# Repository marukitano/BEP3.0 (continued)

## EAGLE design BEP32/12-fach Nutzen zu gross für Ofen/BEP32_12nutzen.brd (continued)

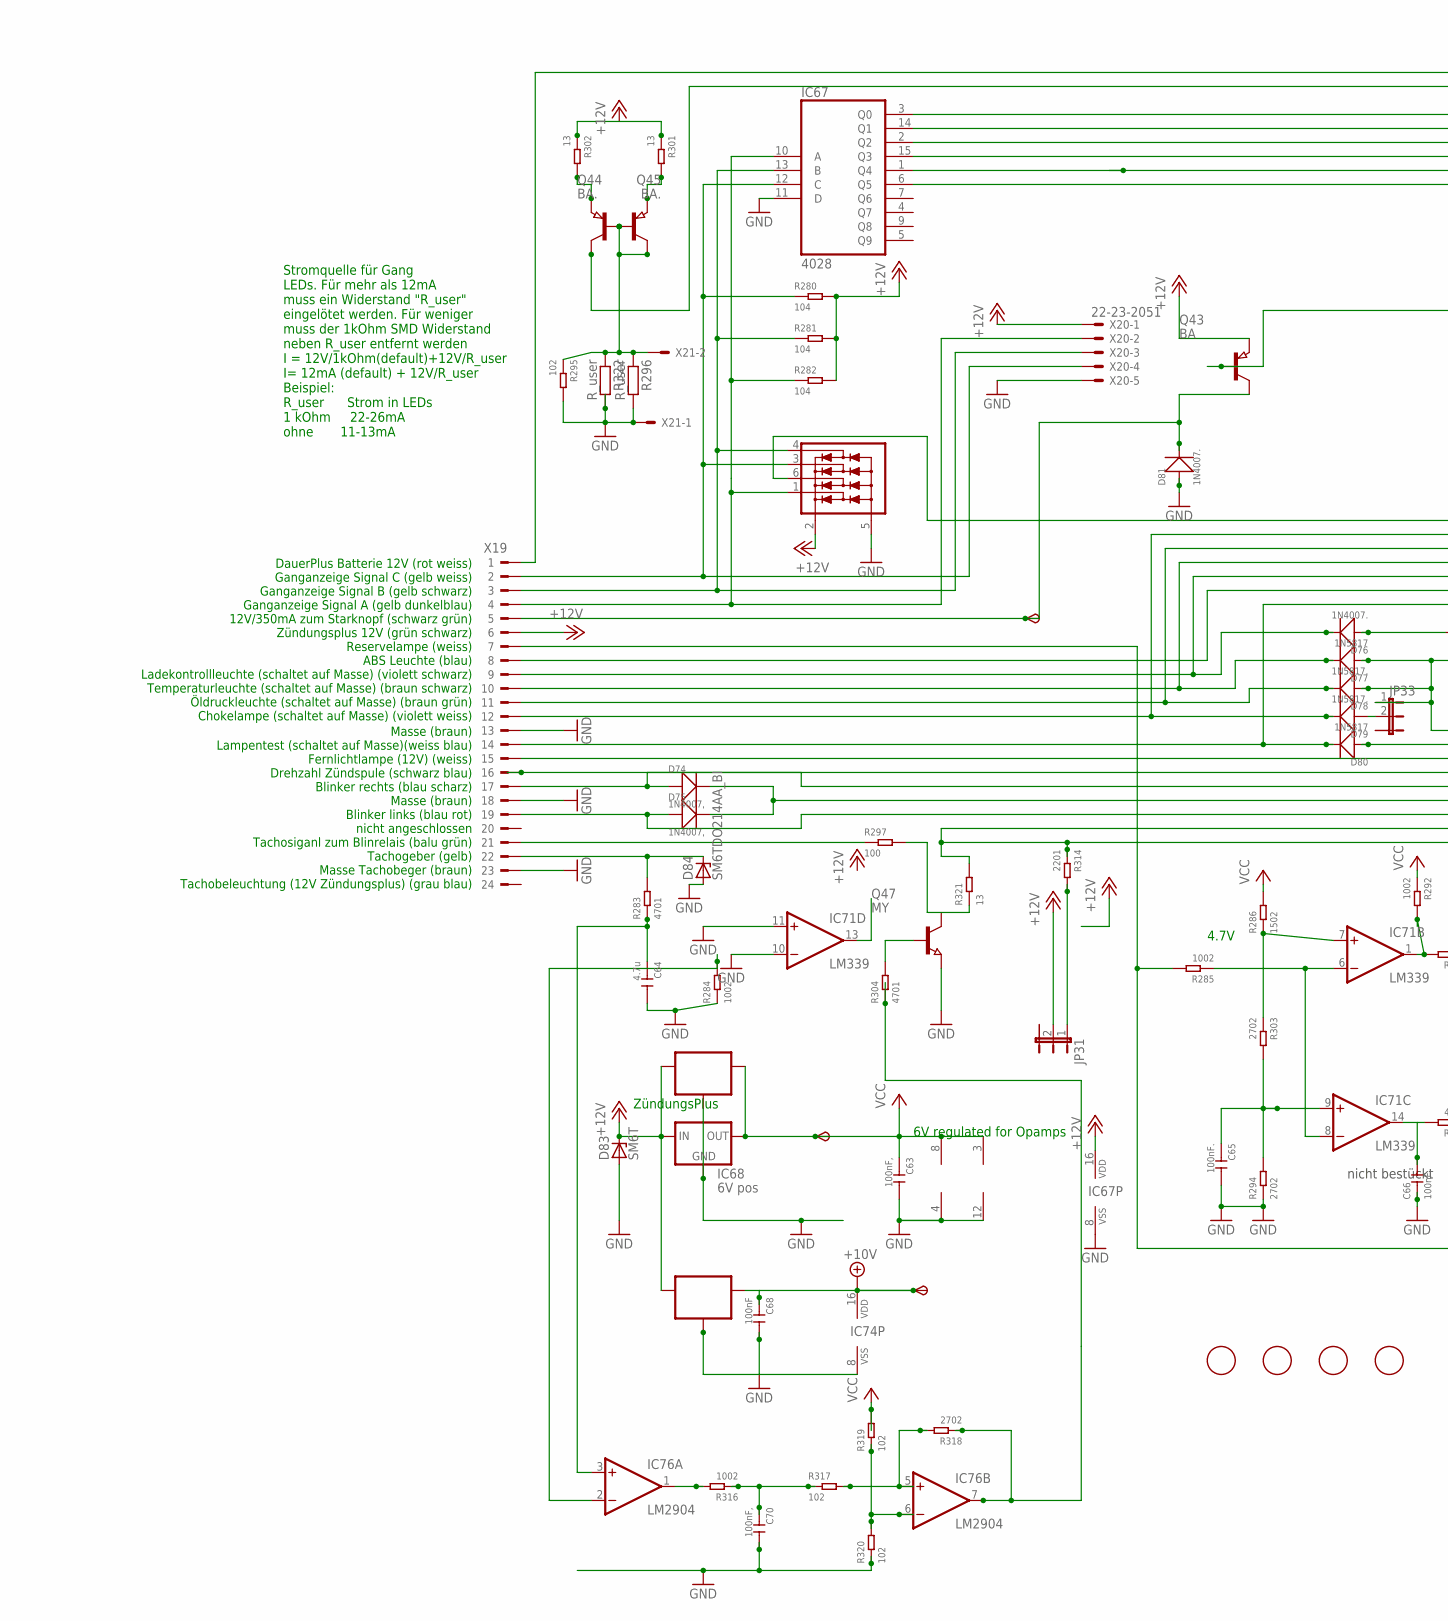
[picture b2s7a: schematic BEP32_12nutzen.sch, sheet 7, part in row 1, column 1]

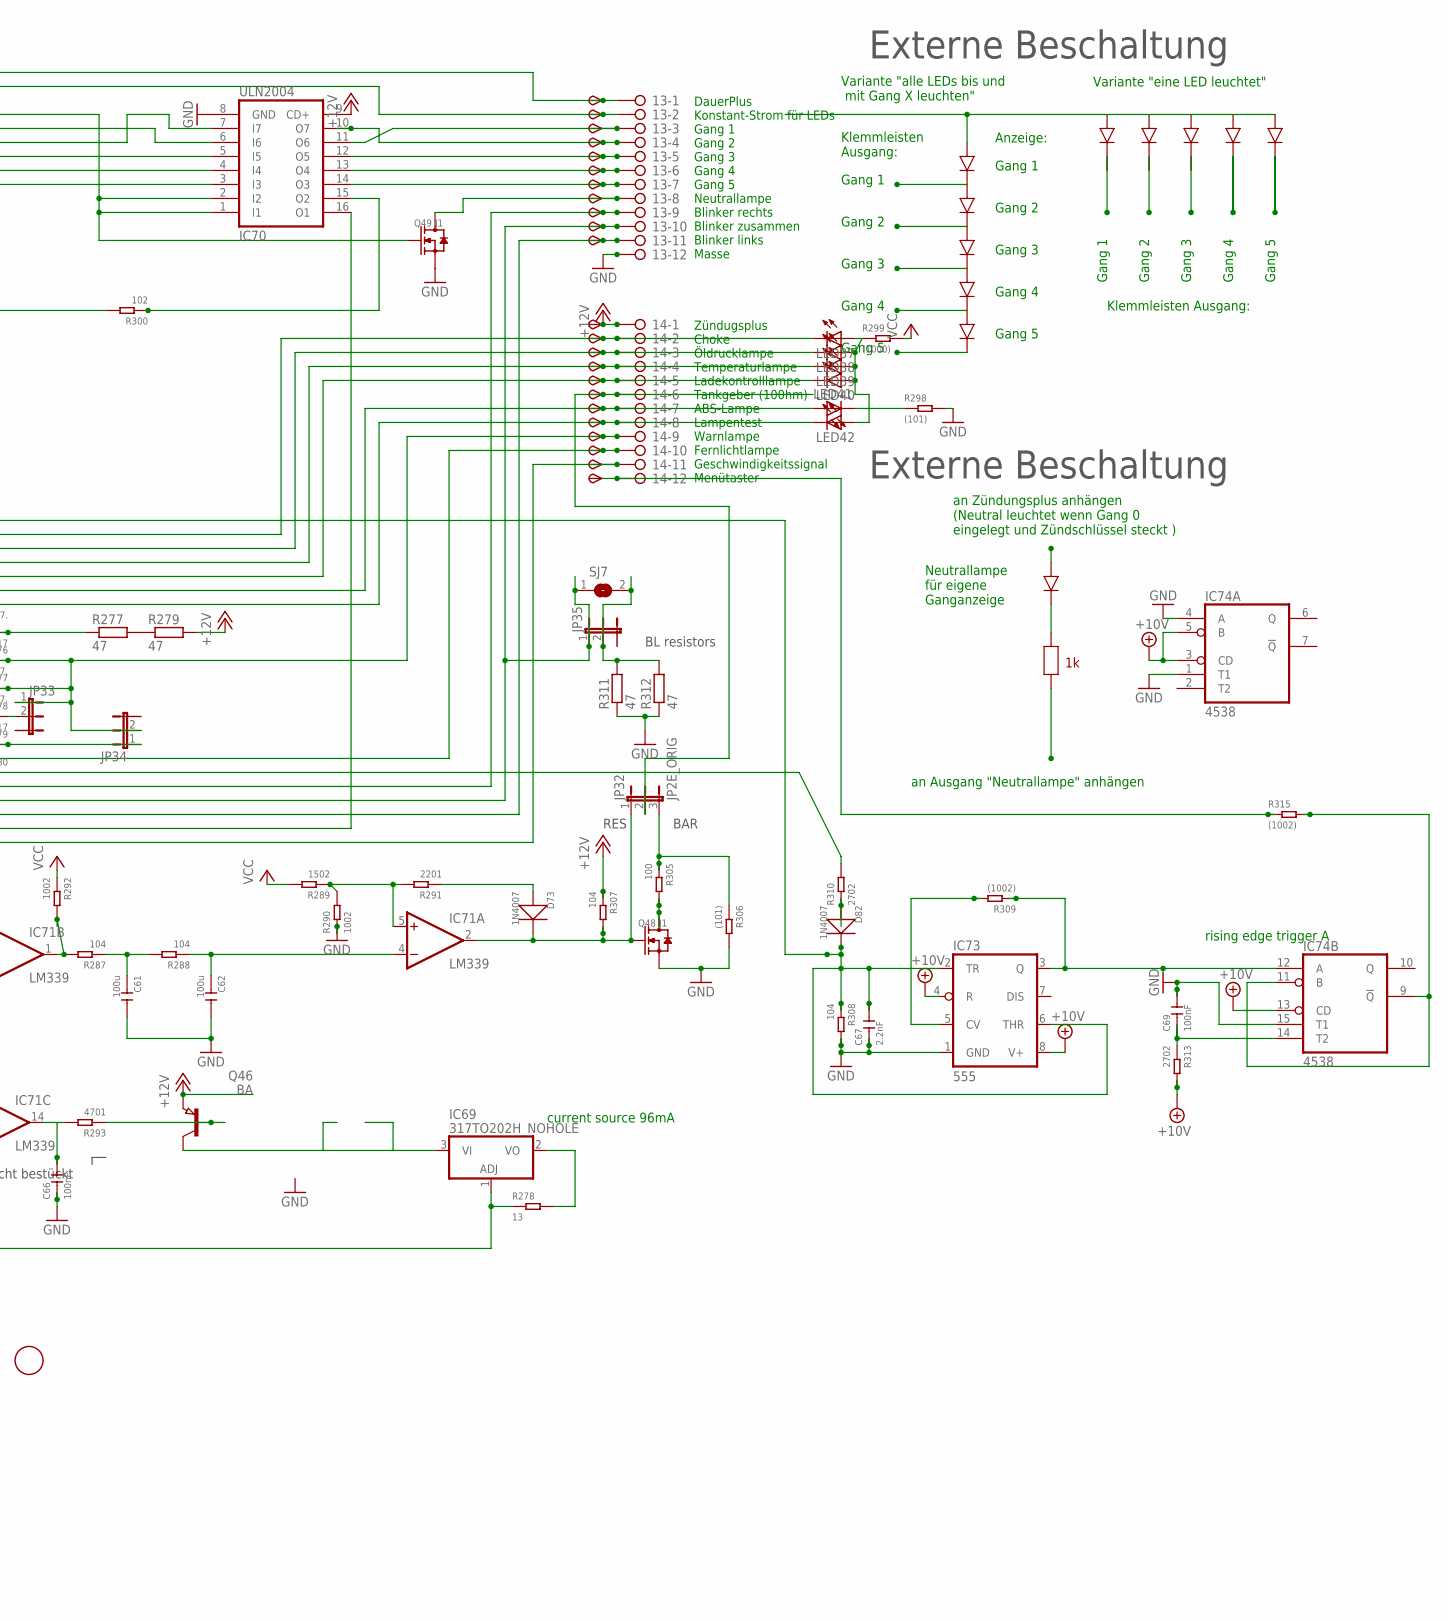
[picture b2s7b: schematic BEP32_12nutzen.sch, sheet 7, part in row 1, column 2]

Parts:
6V6, 10V6: TPSB2.0; B2.0
13, 14: 2081-1132; 12-PIN
C61, C62: 100u; C1206
C63, C70: 100nF,; C0805
C64: 4.7u; C0805
C65, C66: 100nF.; C0805
C67: 2.2nF; C0805
C68, C69: 100nF; C0805
D73, D82: 1N4007; DO-214AC
D74, D75: 1N4007,; DO-214AC
D76, D81: 1N4007.; DO-214AC
D77, D80: 1N5817; DO-214AC_SLIM
D78, D79: 1N5817.; DO-214AC_SLIM
D83: SM6T; DO214AA
D84: SM6TDO214AA_BI; DO214AA_BI
FID25, FID26, FID27, FID28: FIDUCIAL; FIDUCIAL_1MM
IC67: 4028; SO16
IC68: 6V pos; 78LXX
IC69: 317TO202H_NOHOLE; TO220H_NOHOLE
IC70: ULN2004; SO16
IC71: LM339; SO14
IC72: 78L06; SOT89_ROUND
IC73: 555; SO08
IC74: 4538; SO16
IC75: 78L10; SOT89_ROUND
IC76: LM2904; SO08
IC77: NUP4304SOT457_R; SOT457R_PHILIPS
JP31, JP33, JP34, JP35: JP2EJP2_SMALLPADS; JP2_SMALLPADS
JP32: JP2E_ORIG; JP2_ORIG_SMALLPADS
LED37, LED38, LED39, LED40, LED41, LED42: LEDLD260; LD260
Q43, Q46: BA; SOT89
Q44, Q45: BA.; SOT89
Q47: MY; SOT89
Q48, Q49: J1; SOT-23
R277, R279, R311, R312: 47; V235/17_1MM
R278, R301, R302, R321: 13; R1206
R280, R281, R282, R287, R288, R307, R308: 104; R0805
R283, R293, R304: 4701; R0805
R284, R285, R290, R292, R316: 1002; R0805
R286, R289: 1502; R0805
R291, R314: 2201; R0805
R294, R303, R310, R313, R318: 2702; R0805
R295, R300, R317, R319, R320: 102; R0805
R296, R322: R_user; R0805
R297, R305: 100; R0805
R298, R306: (101); R0805
R299: (1000); R0805
R309, R315: (1002); R0805
SJ7: SJ
START6: TPSB2.0; B2.0
TP139, TP140, TP141, TP142, TP143, TP144, TP145, TP146, TP147, TP148, TP149, TP150, TP151, TP152, TP153, TP154, TP155, TP156, TP158, TP159, TP160, TP161: TPSB2.0; B2.0
TP157: TPSB1,27; B1,27
X19: CON_BMWV2; 24-PIN_V2
X20: 22-23-2051
X21: 22-23-2021

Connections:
+10V: 10V6.TP, C68.1, IC73.4 (R), IC73.8 (V+), IC74.3 (CD), IC74.5 (B), IC74.13 (CD), IC74.16 (VDD), IC75.1 (OUT), R313.2; also elsewhere on the board
+12V: 14.1, D83.C, IC67.16 (VDD), IC68.IN, IC70.9 (CD+), IC72.3 (IN), IC75.3 (IN), IC77.2 (V+), JP31.2, Q43.3 (E), Q46.3 (E), R279.2, R280.2, R281.2, R282.2, R301.1, R302.1, R307.1, TP160.TP, X19.6, X20.1; also elsewhere on the board
+12V7: IC76.7 (OUT), R304.1, R318.1
GND: 13.12, C61.2, C62.2, C63.2, C64.2, C65.2, C66.1, C67.1, C68.2, C69.2, C70.2, D81.1 (+), D83.A, D84.A, IC67.8 (VSS), IC67.11 (D), IC68.GND, IC70.8 (GND), IC71.10 (-IN), IC71.11 (+IN), IC71.12 (GND), IC72.2 (GND), IC72.2@1 (GND), IC73.1 (GND), IC74.1 (T1), IC74.4 (A), IC74.8 (VSS), IC74.15 (T1), IC75.2 (GND), IC75.2@1 (GND), IC76.4 (V-), IC77.5 (V-), Q47.3 (E), Q48.2 (S), Q49.2 (S), R284.1, R290.1, R294.1, R295.2, R296.2, R298.2, R306.2, R308.2, R311.1, R312.1, R320.1, R322.2, X19.13, X19.18, X19.23, X20.5, X21.1; also elsewhere on the board
unnamed: R277.2, R279.1
unnamed: 14.9, D77.1 (+), D78.1 (+), JP33.1, JP34.2, TP157.TP
unnamed: IC67.10 (A), IC77.1 (D1), R282.1, X19.4, X20.2
unnamed: IC67.13 (B), IC77.4 (D4), R281.1, X19.3, X20.3
unnamed: D81.2 (-), Q43.2 (C), START6.TP, X19.5
unnamed: IC67.12 (C), IC77.3 (D3), R280.1, X19.2, X20.4
unnamed: 14.7, LED41.A, TP155.TP, X19.8
unnamed: 14.2, D79.2 (-), LED37.K (C), TP150.TP, X19.12
unnamed: 14.3, D78.2 (-), LED38.K (C), TP151.TP, X19.11
unnamed: 14.4, D77.2 (-), LED39.K (C), TP152.TP, X19.10
unnamed: 14.8, D80.2 (-), LED42.K (C), TP156.TP, X19.14
unnamed: 13.9, D74.1 (+), TP147.TP, X19.17
unnamed: 13.11, D75.1 (+), TP149.TP, X19.19
unnamed: D84.C, R283.2, X19.22
unnamed: C64.1, IC76.3 (+IN), R283.1
unnamed: 14.11, IC70.16 (O1), R314.1, R321.2, TP159.TP
unnamed: IC71.1 (OUT), R287.2, R292.2
unnamed: C61.1, R287.1, R288.2
unnamed: C62.1, IC71.4 (-IN), R288.1
unnamed: IC71.5 (+IN), R289.1, R290.2, R291.2
unnamed: D73.1 (+), R291.1
unnamed: C65.1, IC71.9 (+IN), R294.2, R303.2
unnamed: C66.2, IC71.14 (OUT), R293.2
unnamed: Q46.1 (B), R293.1
unnamed: IC67.2 (Q2), IC70.7 (I7)
unnamed: 13.5, IC70.12 (O5), TP143.TP
unnamed: IC67.1 (Q4), IC70.4 (I4)
unnamed: 13.8, Q49.3 (D), TP146.TP
unnamed: 14.10, TP158.TP, X19.15
unnamed: 14.5, D76.2 (-), LED40.K (C), TP153.TP, X19.9
unnamed: D76.1 (+), R277.1
unnamed: IC67.6 (Q5), IC70.3 (I3)
unnamed: 13.4, IC70.10 (O7), TP142.TP
unnamed: IC69.1 (ADJ), R278.1, R285.2, X19.7
unnamed: IC71.6 (-IN), IC71.8 (-IN), R285.1
unnamed: 13.2, Q45.2 (C), TP140.TP
unnamed: 13.1, TP139.TP, X19.1
unnamed: R310.2, X19.16
unnamed: IC67.15 (Q3), IC70.5 (I5)
unnamed: 13.6, IC70.13 (O4), TP144.TP
unnamed: 13.7, IC70.14 (O3), TP145.TP
unnamed: 14.6, JP32.2, TP154.TP
unnamed: LED41.K (C), R298.1
unnamed: LED37.A, LED38.A, LED39.A, LED40.A, LED42.A, R299.1
unnamed: Q43.1 (B), R300.2
unnamed: IC67.3 (Q0), IC70.1 (I1), IC70.2 (I2), Q49.1 (G)
unnamed: IC67.14 (Q1), IC70.6 (I6)
unnamed: 13.3, IC70.11 (O6), TP141.TP
unnamed: Q44.1 (B), Q44.2 (C), Q45.1 (B), R295.1, R296.1, R322.1, X21.2
unnamed: Q45.3 (E), R302.2
unnamed: Q44.3 (E), R301.2
unnamed: IC71.7 (+IN), R286.1, R303.1
unnamed: IC76.2 (-IN), R284.2
unnamed: Q47.1 (B), R304.2
unnamed: Q48.3 (D), R305.2
unnamed: IC69.2 (VO), R278.2
unnamed: IC69.3 (VI), Q46.2 (C)
unnamed: C67.2, D82.2 (-), IC73.2 (TR), IC73.6 (THR), IC77.6 (D2), R308.1
unnamed: IC73.5 (CV), R309.2
unnamed: IC73.3 (Q), IC74.12 (A), R309.1
unnamed: D82.1 (+), R310.1
unnamed: 13.10, D74.2 (-), D75.2 (-), JP35.1, SJ7.1, TP148.TP
unnamed: JP35.2, R311.2, R312.2, SJ7.2
unnamed: IC74.9 (!Q), IC74.11 (B), R315.2
unnamed: C69.1, IC74.14 (T2), R313.1
unnamed: JP31.1, R314.2
unnamed: IC70.15 (O2), R300.1
unnamed: 14.12, R315.1, TP161.TP
unnamed: D79.1 (+), JP33.2
unnamed: D73.2 (-), IC71.2 (OUT), JP32.1, Q48.1 (G), R307.2
unnamed: IC76.1 (OUT), R316.2
unnamed: C70.1, R316.1, R317.1
unnamed: IC76.5 (+IN), R317.2, R318.2
unnamed: IC76.6 (-IN), R319.1, R320.2
unnamed: D80.1 (+), JP34.1
unnamed: JP32.3, R305.1, R306.1
unnamed: R297.1, X19.21
unnamed: Q47.2 (C), R297.2, R321.1
VCC: 6V6.TP, C63.1, IC68.OUT, IC71.3 (V+), IC72.1 (OUT), IC76.8 (V+), R286.2, R289.2, R292.1, R299.2, R319.2; also elsewhere on the board

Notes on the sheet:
6V regulated for Opamps
current source 96mA
ZündungsPlus
Zündugsplus Choke Öldrucklampe Temperaturlampe Ladekontrolllampe Tankgeber (100hm) ABS-Lampe Lampentest Warnlampe Fernlichtlampe Geschwindigkeitssignal Menütaster
DauerPlus Konstant-Strom für LEDs Gang 1 Gang 2 Gang 3 Gang 4 Gang 5 Neutrallampe Blinker rechts Blinker zusammen Blinker links Masse
DauerPlus Batterie 12V (rot weiss) Ganganzeige Signal C (gelb weiss) Ganganzeige Signal B (gelb schwarz) Ganganzeige Signal A (gelb dunkelblau) 12V/350mA zum Starknopf (schwarz grün) Zündungsplus 12V (grün schwarz) Reservelampe (weiss) ABS Leuchte (blau) Ladekontrollleuchte (schaltet auf Masse) (vi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
Masse (braun) Lampentest (schaltet auf Masse)(weiss blau) Fernlichtlampe (12V) (weiss) Drehzahl Zündspule (schwarz blau) Blinker rechts (blau scharz) Masse (braun) Blinker links (blau rot) nicht angeschlossen Tachosiganl zum Blinrelais (balu grün) Tachogeber (gelb) Masse Tachobeger (braun) Tachobel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
4.7V
Stromquelle für Gang LEDs. Für mehr als 12mA muss ein Widerstand "R_user" eingelötet werden. Für weniger muss der 1kOhm SMD Widerstand neben R_user entfernt werden I = 12V/1kOhm(default)+12V/R_user I= 12mA (default) + 12V/R_user Beispiel: R_user Strom in LEDs 1 kOhm 22-26mA ohne 11-13mA
Gang 1
Gang 2
Gang 3
Gang 4
Gang 5
Variante "eine LED leuchtet"
Variante "alle LEDs bis und mit Gang X leuchten"
Klemmleisten Ausgang:
Klemmleisten Ausgang:
an Zündungsplus anhängen (Neutral leuchtet wenn Gang 0 eingelegt und Zündschlüssel steckt )
an Ausgang "Neutrallampe" anhängen
Neutrallampe für eigene Ganganzeige
Externe Beschaltung
Anzeige:
nicht bestückt
rising edge trigger A
BAR
RES
BL resistors

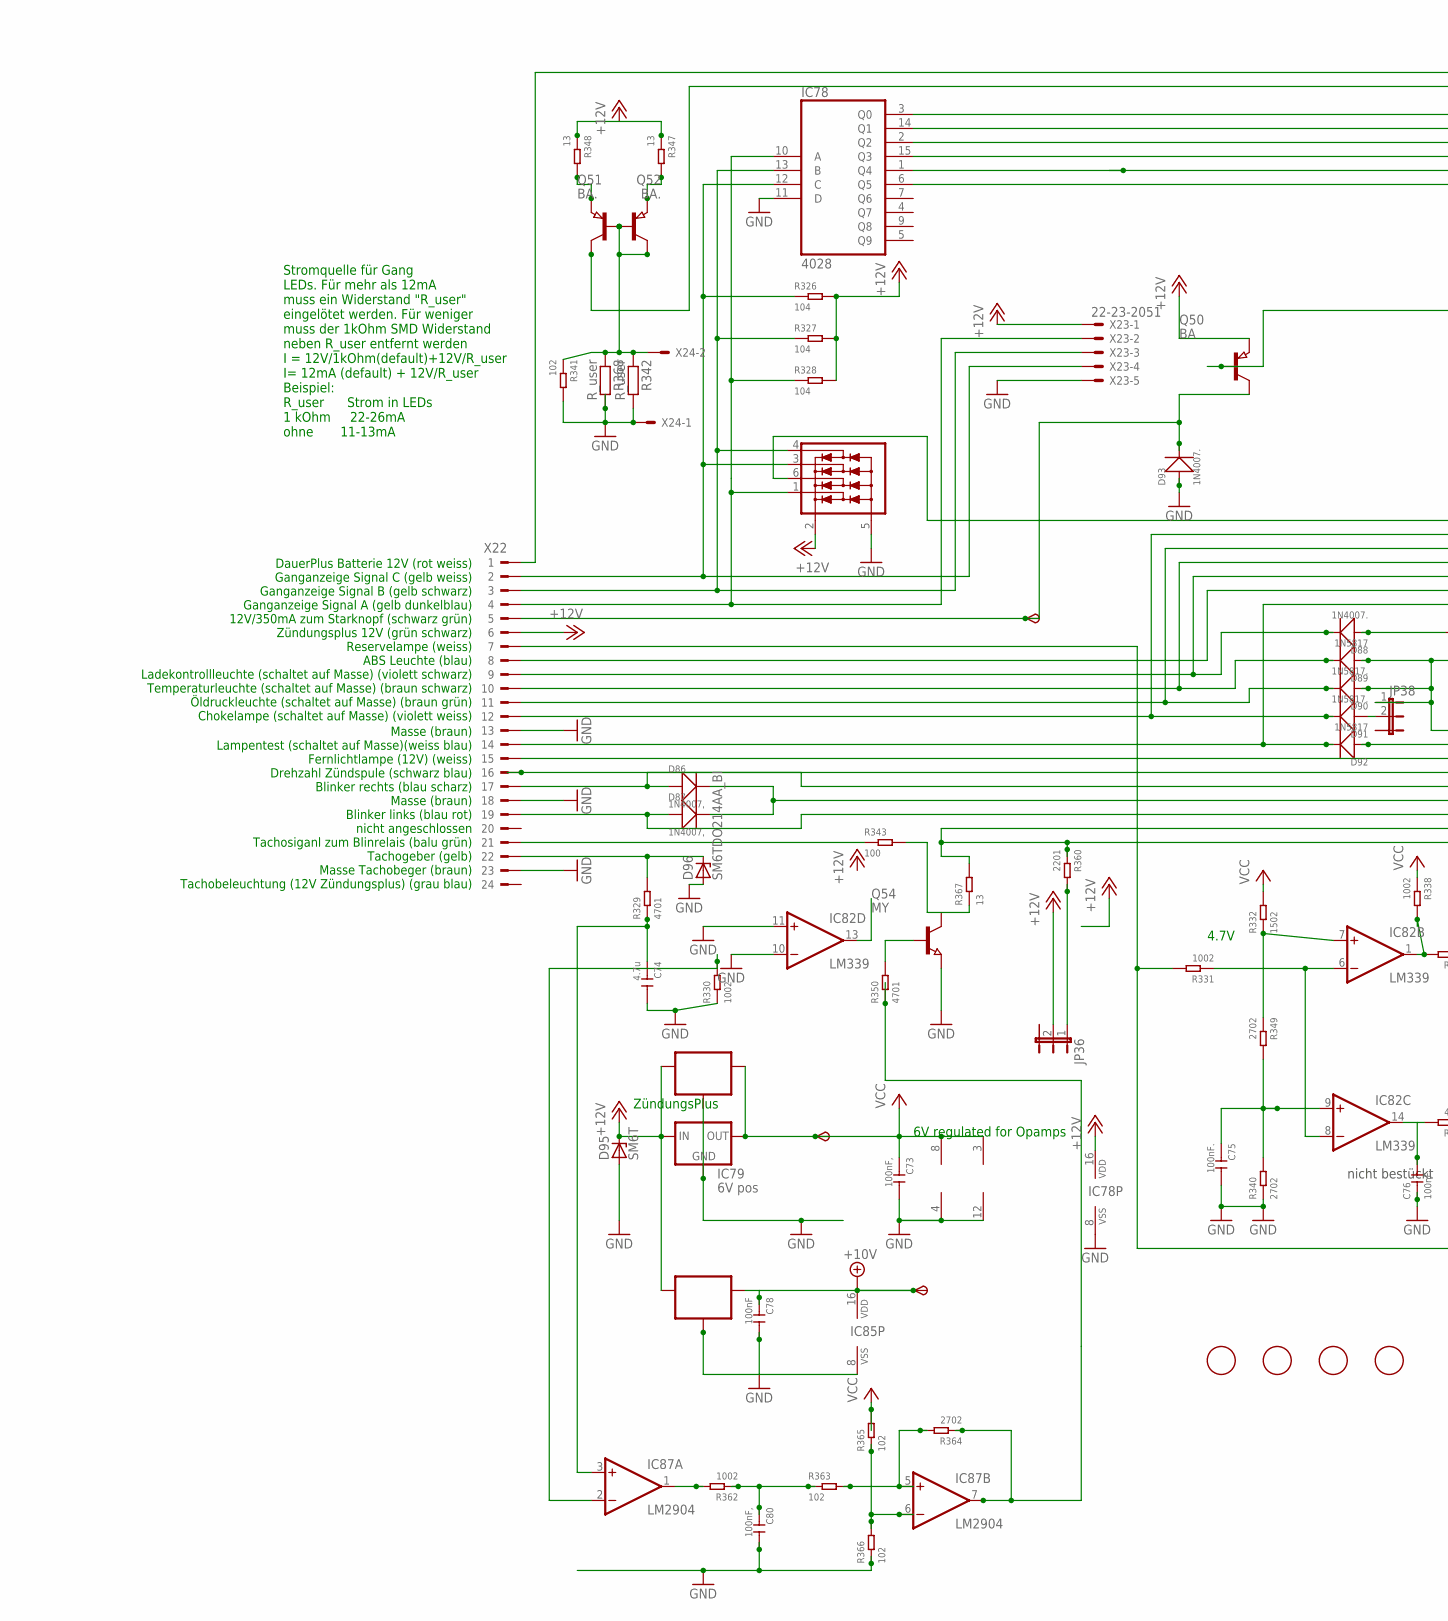
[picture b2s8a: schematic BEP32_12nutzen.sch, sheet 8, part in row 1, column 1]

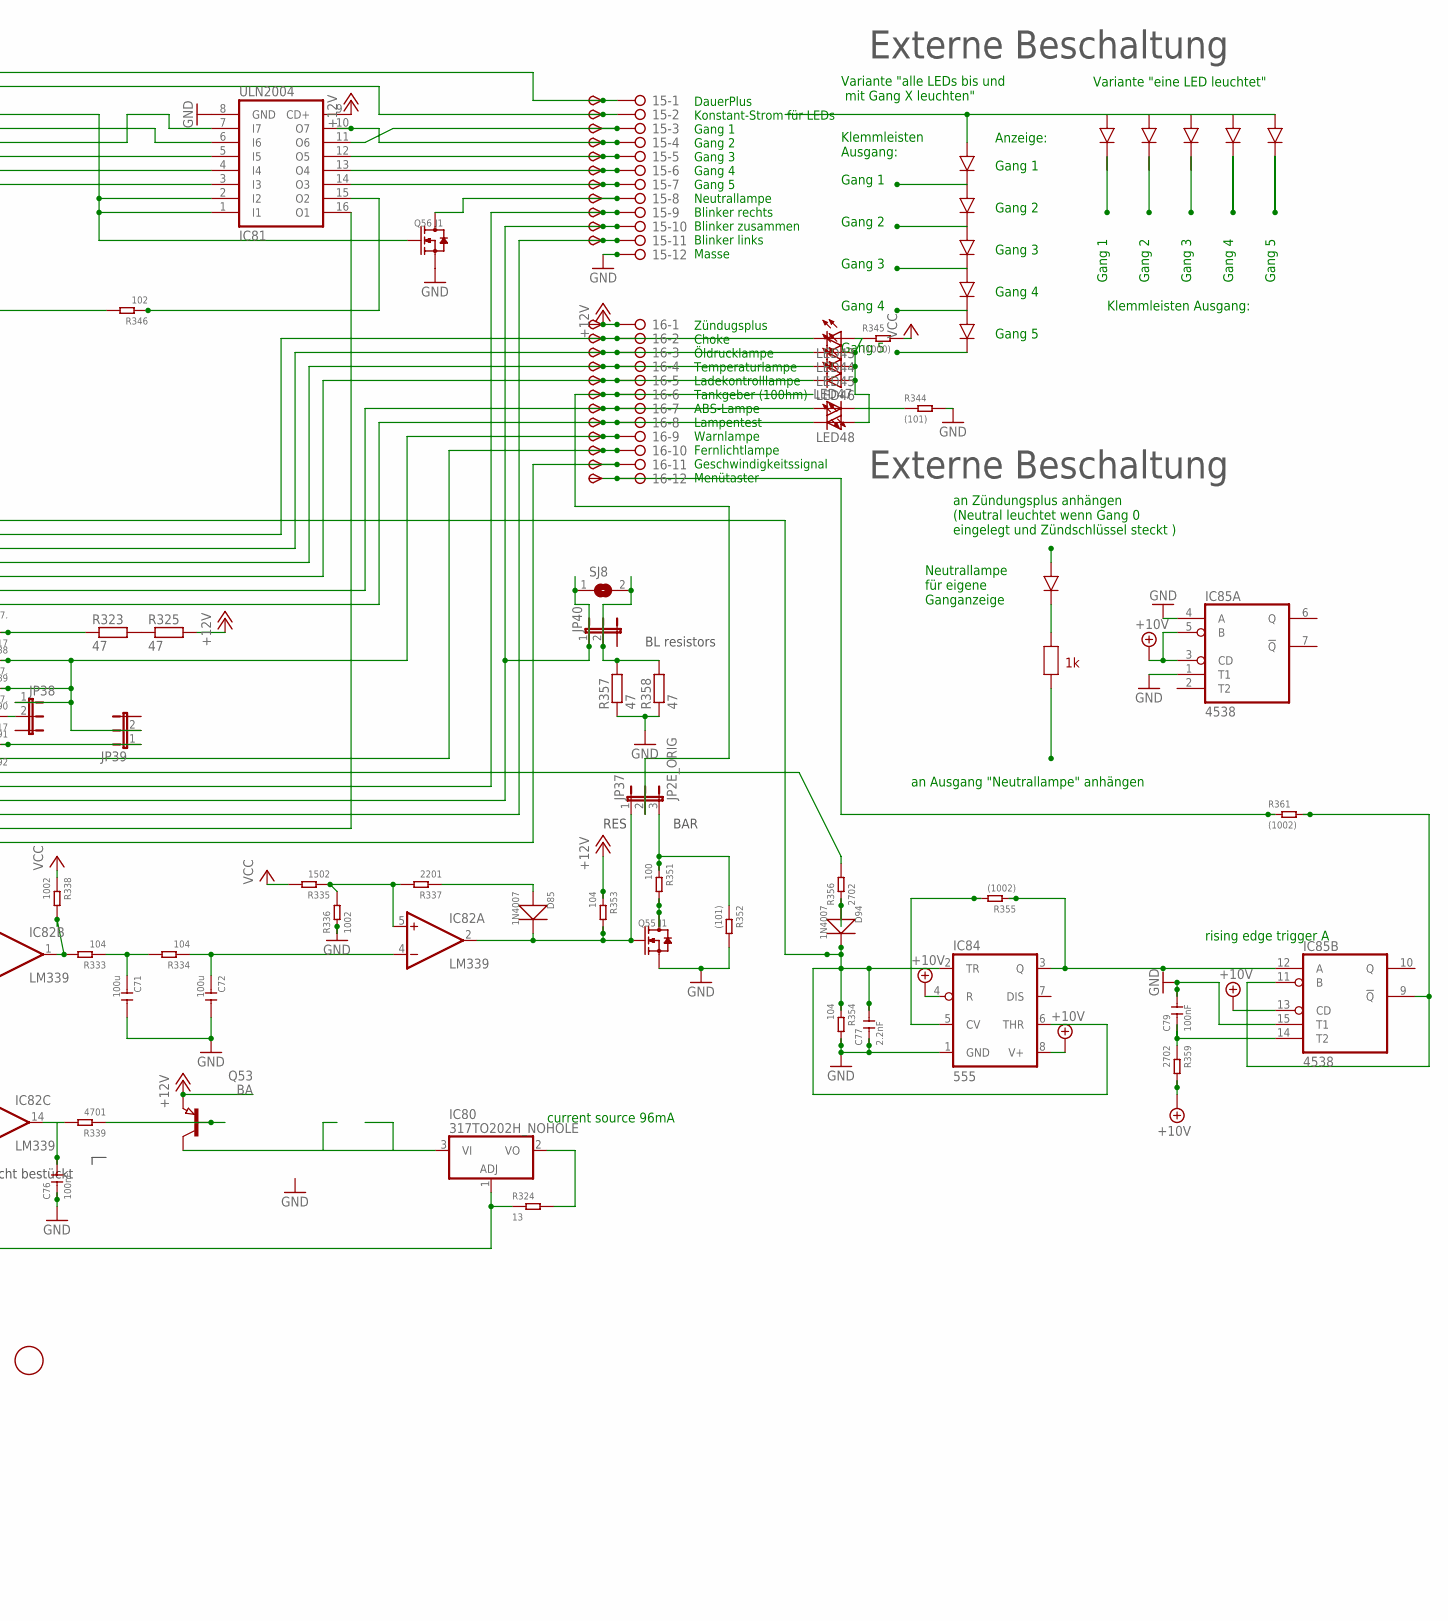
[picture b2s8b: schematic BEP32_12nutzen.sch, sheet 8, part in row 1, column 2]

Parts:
6V7, 10V7: TPSB2.0; B2.0
15, 16: 2081-1132; 12-PIN
C71, C72: 100u; C1206
C73, C80: 100nF,; C0805
C74: 4.7u; C0805
C75, C76: 100nF.; C0805
C77: 2.2nF; C0805
C78, C79: 100nF; C0805
D85, D94: 1N4007; DO-214AC
D86, D87: 1N4007,; DO-214AC
D88, D93: 1N4007.; DO-214AC
D89, D92: 1N5817; DO-214AC_SLIM
D90, D91: 1N5817.; DO-214AC_SLIM
D95: SM6T; DO214AA
D96: SM6TDO214AA_BI; DO214AA_BI
FID29, FID30, FID31, FID32: FIDUCIAL; FIDUCIAL_1MM
IC78: 4028; SO16
IC79: 6V pos; 78LXX
IC80: 317TO202H_NOHOLE; TO220H_NOHOLE
IC81: ULN2004; SO16
IC82: LM339; SO14
IC83: 78L06; SOT89_ROUND
IC84: 555; SO08
IC85: 4538; SO16
IC86: 78L10; SOT89_ROUND
IC87: LM2904; SO08
IC88: NUP4304SOT457_R; SOT457R_PHILIPS
JP36, JP38, JP39, JP40: JP2EJP2_SMALLPADS; JP2_SMALLPADS
JP37: JP2E_ORIG; JP2_ORIG_SMALLPADS
LED43, LED44, LED45, LED46, LED47, LED48: LEDLD260; LD260
Q50, Q53: BA; SOT89
Q51, Q52: BA.; SOT89
Q54: MY; SOT89
Q55, Q56: J1; SOT-23
R323, R325, R357, R358: 47; V235/17_1MM
R324, R347, R348, R367: 13; R1206
R326, R327, R328, R333, R334, R353, R354: 104; R0805
R329, R339, R350: 4701; R0805
R330, R331, R336, R338, R362: 1002; R0805
R332, R335: 1502; R0805
R337, R360: 2201; R0805
R340, R349, R356, R359, R364: 2702; R0805
R341, R346, R363, R365, R366: 102; R0805
R342, R368: R_user; R0805
R343, R351: 100; R0805
R344, R352: (101); R0805
R345: (1000); R0805
R355, R361: (1002); R0805
SJ8: SJ
START7: TPSB2.0; B2.0
TP162, TP163, TP164, TP165, TP166, TP167, TP168, TP169, TP170, TP171, TP172, TP173, TP174, TP175, TP176, TP177, TP178, TP179, TP181, TP182, TP183, TP184: TPSB2.0; B2.0
TP180: TPSB1,27; B1,27
X22: CON_BMWV2; 24-PIN_V2
X23: 22-23-2051
X24: 22-23-2021

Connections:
+10V: 10V7.TP, C78.1, IC84.4 (R), IC84.8 (V+), IC85.3 (CD), IC85.5 (B), IC85.13 (CD), IC85.16 (VDD), IC86.1 (OUT), R359.2; also elsewhere on the board
+12V: 16.1, D95.C, IC78.16 (VDD), IC79.IN, IC81.9 (CD+), IC83.3 (IN), IC86.3 (IN), IC88.2 (V+), JP36.2, Q50.3 (E), Q53.3 (E), R325.2, R326.2, R327.2, R328.2, R347.1, R348.1, R353.1, TP183.TP, X22.6, X23.1; also elsewhere on the board
+12V8: IC87.7 (OUT), R350.1, R364.1
GND: 15.12, C71.2, C72.2, C73.2, C74.2, C75.2, C76.1, C77.1, C78.2, C79.2, C80.2, D93.1 (+), D95.A, D96.A, IC78.8 (VSS), IC78.11 (D), IC79.GND, IC81.8 (GND), IC82.10 (-IN), IC82.11 (+IN), IC82.12 (GND), IC83.2 (GND), IC83.2@1 (GND), IC84.1 (GND), IC85.1 (T1), IC85.4 (A), IC85.8 (VSS), IC85.15 (T1), IC86.2 (GND), IC86.2@1 (GND), IC87.4 (V-), IC88.5 (V-), Q54.3 (E), Q55.2 (S), Q56.2 (S), R330.1, R336.1, R340.1, R341.2, R342.2, R344.2, R352.2, R354.2, R357.1, R358.1, R366.1, R368.2, X22.13, X22.18, X22.23, X23.5, X24.1; also elsewhere on the board
unnamed: R323.2, R325.1
unnamed: 16.9, D89.1 (+), D90.1 (+), JP38.1, JP39.2, TP180.TP
unnamed: IC78.10 (A), IC88.1 (D1), R328.1, X22.4, X23.2
unnamed: IC78.13 (B), IC88.4 (D4), R327.1, X22.3, X23.3
unnamed: D93.2 (-), Q50.2 (C), START7.TP, X22.5
unnamed: IC78.12 (C), IC88.3 (D3), R326.1, X22.2, X23.4
unnamed: 16.7, LED47.A, TP178.TP, X22.8
unnamed: 16.2, D91.2 (-), LED43.K (C), TP173.TP, X22.12
unnamed: 16.3, D90.2 (-), LED44.K (C), TP174.TP, X22.11
unnamed: 16.4, D89.2 (-), LED45.K (C), TP175.TP, X22.10
unnamed: 16.8, D92.2 (-), LED48.K (C), TP179.TP, X22.14
unnamed: 15.9, D86.1 (+), TP170.TP, X22.17
unnamed: 15.11, D87.1 (+), TP172.TP, X22.19
unnamed: D96.C, R329.2, X22.22
unnamed: C74.1, IC87.3 (+IN), R329.1
unnamed: 16.11, IC81.16 (O1), R360.1, R367.2, TP182.TP
unnamed: IC82.1 (OUT), R333.2, R338.2
unnamed: C71.1, R333.1, R334.2
unnamed: C72.1, IC82.4 (-IN), R334.1
unnamed: IC82.5 (+IN), R335.1, R336.2, R337.2
unnamed: D85.1 (+), R337.1
unnamed: C75.1, IC82.9 (+IN), R340.2, R349.2
unnamed: C76.2, IC82.14 (OUT), R339.2
unnamed: Q53.1 (B), R339.1
unnamed: IC78.2 (Q2), IC81.7 (I7)
unnamed: 15.5, IC81.12 (O5), TP166.TP
unnamed: IC78.1 (Q4), IC81.4 (I4)
unnamed: 15.8, Q56.3 (D), TP169.TP
unnamed: 16.10, TP181.TP, X22.15
unnamed: 16.5, D88.2 (-), LED46.K (C), TP176.TP, X22.9
unnamed: D88.1 (+), R323.1
unnamed: IC78.6 (Q5), IC81.3 (I3)
unnamed: 15.4, IC81.10 (O7), TP165.TP
unnamed: IC80.1 (ADJ), R324.1, R331.2, X22.7
unnamed: IC82.6 (-IN), IC82.8 (-IN), R331.1
unnamed: 15.2, Q52.2 (C), TP163.TP
unnamed: 15.1, TP162.TP, X22.1
unnamed: R356.2, X22.16
unnamed: IC78.15 (Q3), IC81.5 (I5)
unnamed: 15.6, IC81.13 (O4), TP167.TP
unnamed: 15.7, IC81.14 (O3), TP168.TP
unnamed: 16.6, JP37.2, TP177.TP
unnamed: LED47.K (C), R344.1
unnamed: LED43.A, LED44.A, LED45.A, LED46.A, LED48.A, R345.1
unnamed: Q50.1 (B), R346.2
unnamed: IC78.3 (Q0), IC81.1 (I1), IC81.2 (I2), Q56.1 (G)
unnamed: IC78.14 (Q1), IC81.6 (I6)
unnamed: 15.3, IC81.11 (O6), TP164.TP
unnamed: Q51.1 (B), Q51.2 (C), Q52.1 (B), R341.1, R342.1, R368.1, X24.2
unnamed: Q52.3 (E), R348.2
unnamed: Q51.3 (E), R347.2
unnamed: IC82.7 (+IN), R332.1, R349.1
unnamed: IC87.2 (-IN), R330.2
unnamed: Q54.1 (B), R350.2
unnamed: Q55.3 (D), R351.2
unnamed: IC80.2 (VO), R324.2
unnamed: IC80.3 (VI), Q53.2 (C)
unnamed: C77.2, D94.2 (-), IC84.2 (TR), IC84.6 (THR), IC88.6 (D2), R354.1
unnamed: IC84.5 (CV), R355.2
unnamed: IC84.3 (Q), IC85.12 (A), R355.1
unnamed: D94.1 (+), R356.1
unnamed: 15.10, D86.2 (-), D87.2 (-), JP40.1, SJ8.1, TP171.TP
unnamed: JP40.2, R357.2, R358.2, SJ8.2
unnamed: IC85.9 (!Q), IC85.11 (B), R361.2
unnamed: C79.1, IC85.14 (T2), R359.1
unnamed: JP36.1, R360.2
unnamed: IC81.15 (O2), R346.1
unnamed: 16.12, R361.1, TP184.TP
unnamed: D91.1 (+), JP38.2
unnamed: D85.2 (-), IC82.2 (OUT), JP37.1, Q55.1 (G), R353.2
unnamed: IC87.1 (OUT), R362.2
unnamed: C80.1, R362.1, R363.1
unnamed: IC87.5 (+IN), R363.2, R364.2
unnamed: IC87.6 (-IN), R365.1, R366.2
unnamed: D92.1 (+), JP39.1
unnamed: JP37.3, R351.1, R352.1
unnamed: R343.1, X22.21
unnamed: Q54.2 (C), R343.2, R367.1
VCC: 6V7.TP, C73.1, IC79.OUT, IC82.3 (V+), IC83.1 (OUT), IC87.8 (V+), R332.2, R335.2, R338.1, R345.2, R365.2; also elsewhere on the board

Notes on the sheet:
6V regulated for Opamps
current source 96mA
ZündungsPlus
Zündugsplus Choke Öldrucklampe Temperaturlampe Ladekontrolllampe Tankgeber (100hm) ABS-Lampe Lampentest Warnlampe Fernlichtlampe Geschwindigkeitssignal Menütaster
DauerPlus Konstant-Strom für LEDs Gang 1 Gang 2 Gang 3 Gang 4 Gang 5 Neutrallampe Blinker rechts Blinker zusammen Blinker links Masse
DauerPlus Batterie 12V (rot weiss) Ganganzeige Signal C (gelb weiss) Ganganzeige Signal B (gelb schwarz) Ganganzeige Signal A (gelb dunkelblau) 12V/350mA zum Starknopf (schwarz grün) Zündungsplus 12V (grün schwarz) Reservelampe (weiss) ABS Leuchte (blau) Ladekontrollleuchte (schaltet auf Masse) (vi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
Masse (braun) Lampentest (schaltet auf Masse)(weiss blau) Fernlichtlampe (12V) (weiss) Drehzahl Zündspule (schwarz blau) Blinker rechts (blau scharz) Masse (braun) Blinker links (blau rot) nicht angeschlossen Tachosiganl zum Blinrelais (balu grün) Tachogeber (gelb) Masse Tachobeger (braun) Tachobel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
4.7V
Stromquelle für Gang LEDs. Für mehr als 12mA muss ein Widerstand "R_user" eingelötet werden. Für weniger muss der 1kOhm SMD Widerstand neben R_user entfernt werden I = 12V/1kOhm(default)+12V/R_user I= 12mA (default) + 12V/R_user Beispiel: R_user Strom in LEDs 1 kOhm 22-26mA ohne 11-13mA
Gang 1
Gang 2
Gang 3
Gang 4
Gang 5
Variante "eine LED leuchtet"
Variante "alle LEDs bis und mit Gang X leuchten"
Klemmleisten Ausgang:
Klemmleisten Ausgang:
an Zündungsplus anhängen (Neutral leuchtet wenn Gang 0 eingelegt und Zündschlüssel steckt )
an Ausgang "Neutrallampe" anhängen
Neutrallampe für eigene Ganganzeige
Externe Beschaltung
Anzeige:
nicht bestückt
rising edge trigger A
BAR
RES
BL resistors

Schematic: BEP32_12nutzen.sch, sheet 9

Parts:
6V8, 10V8: TPSB2.0; B2.0
17, 18: 2081-1132; 12-PIN
C81, C82: 100u; C1206
C83, C90: 100nF,; C0805
C84: 4.7u; C0805
C85, C86: 100nF.; C0805
C87: 2.2nF; C0805
C88, C89: 100nF; C0805
D97, D106: 1N4007; DO-214AC
D98, D99: 1N4007,; DO-214AC
D100, D105: 1N4007.; DO-214AC
D101, D104: 1N5817; DO-214AC_SLIM
D102, D103: 1N5817.; DO-214AC_SLIM
D107: SM6T; DO214AA
D108: SM6TDO214AA_BI; DO214AA_BI
FID33, FID34, FID35, FID36: FIDUCIAL; FIDUCIAL_1MM
IC89: 4028; SO16
IC90: 6V pos; 78LXX
IC91: 317TO202H_NOHOLE; TO220H_NOHOLE
IC92: ULN2004; SO16
IC93: LM339; SO14
IC94: 78L06; SOT89_ROUND
IC95: 555; SO08
IC96: 4538; SO16
IC97: 78L10; SOT89_ROUND
IC98: LM2904; SO08
IC99: NUP4304SOT457_R; SOT457R_PHILIPS
JP41, JP43, JP44, JP45: JP2EJP2_SMALLPADS; JP2_SMALLPADS
JP42: JP2E_ORIG; JP2_ORIG_SMALLPADS
LED49, LED50, LED51, LED52, LED53, LED54: LEDLD260; LD260
Q57, Q60: BA; SOT89
Q58, Q59: BA.; SOT89
Q61: MY; SOT89
Q62, Q63: J1; SOT-23
R369, R371, R403, R404: 47; V235/17_1MM
R370, R393, R394, R413: 13; R1206
R372, R373, R374, R379, R380, R399, R400: 104; R0805
R375, R385, R396: 4701; R0805
R376, R377, R382, R384, R408: 1002; R0805
R378, R381: 1502; R0805
R383, R406: 2201; R0805
R386, R395, R402, R405, R410: 2702; R0805
R387, R392, R409, R411, R412: 102; R0805
R388, R414: R_user; R0805
R389, R397: 100; R0805
R390, R398: (101); R0805
R391: (1000); R0805
R401, R407: (1002); R0805
SJ9: SJ
START8: TPSB2.0; B2.0
TP185, TP186, TP187, TP188, TP189, TP190, TP191, TP192, TP193, TP194, TP195, TP196, TP197, TP198, TP199, TP200, TP201, TP202, TP204, TP205, TP206, TP207: TPSB2.0; B2.0
TP203: TPSB1,27; B1,27
X25: CON_BMWV2; 24-PIN_V2
X26: 22-23-2051
X27: 22-23-2021

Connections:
+10V: 10V8.TP, C88.1, IC95.4 (R), IC95.8 (V+), IC96.3 (CD), IC96.5 (B), IC96.13 (CD), IC96.16 (VDD), IC97.1 (OUT), R405.2; also elsewhere on the board
+12V: 18.1, D107.C, IC89.16 (VDD), IC90.IN, IC92.9 (CD+), IC94.3 (IN), IC97.3 (IN), IC99.2 (V+), JP41.2, Q57.3 (E), Q60.3 (E), R371.2, R372.2, R373.2, R374.2, R393.1, R394.1, R399.1, TP206.TP, X25.6, X26.1; also elsewhere on the board
+12V9: IC98.7 (OUT), R396.1, R410.1
GND: 17.12, C81.2, C82.2, C83.2, C84.2, C85.2, C86.1, C87.1, C88.2, C89.2, C90.2, D105.1 (+), D107.A, D108.A, IC89.8 (VSS), IC89.11 (D), IC90.GND, IC92.8 (GND), IC93.10 (-IN), IC93.11 (+IN), IC93.12 (GND), IC94.2 (GND), IC94.2@1 (GND), IC95.1 (GND), IC96.1 (T1), IC96.4 (A), IC96.8 (VSS), IC96.15 (T1), IC97.2 (GND), IC97.2@1 (GND), IC98.4 (V-), IC99.5 (V-), Q61.3 (E), Q62.2 (S), Q63.2 (S), R376.1, R382.1, R386.1, R387.2, R388.2, R390.2, R398.2, R400.2, R403.1, R404.1, R412.1, R414.2, X25.13, X25.18, X25.23, X26.5, X27.1; also elsewhere on the board
unnamed: R369.2, R371.1
unnamed: 18.9, D101.1 (+), D102.1 (+), JP43.1, JP44.2, TP203.TP
unnamed: IC89.10 (A), IC99.1 (D1), R374.1, X25.4, X26.2
unnamed: IC89.13 (B), IC99.4 (D4), R373.1, X25.3, X26.3
unnamed: D105.2 (-), Q57.2 (C), START8.TP, X25.5
unnamed: IC89.12 (C), IC99.3 (D3), R372.1, X25.2, X26.4
unnamed: 18.7, LED53.A, TP201.TP, X25.8
unnamed: 18.2, D103.2 (-), LED49.K (C), TP196.TP, X25.12
unnamed: 18.3, D102.2 (-), LED50.K (C), TP197.TP, X25.11
unnamed: 18.4, D101.2 (-), LED51.K (C), TP198.TP, X25.10
unnamed: 18.8, D104.2 (-), LED54.K (C), TP202.TP, X25.14
unnamed: 17.9, D98.1 (+), TP193.TP, X25.17
unnamed: 17.11, D99.1 (+), TP195.TP, X25.19
unnamed: D108.C, R375.2, X25.22
unnamed: C84.1, IC98.3 (+IN), R375.1
unnamed: 18.11, IC92.16 (O1), R406.1, R413.2, TP205.TP
unnamed: IC93.1 (OUT), R379.2, R384.2
unnamed: C81.1, R379.1, R380.2
unnamed: C82.1, IC93.4 (-IN), R380.1
unnamed: IC93.5 (+IN), R381.1, R382.2, R383.2
unnamed: D97.1 (+), R383.1
unnamed: C85.1, IC93.9 (+IN), R386.2, R395.2
unnamed: C86.2, IC93.14 (OUT), R385.2
unnamed: Q60.1 (B), R385.1
unnamed: IC89.2 (Q2), IC92.7 (I7)
unnamed: 17.5, IC92.12 (O5), TP189.TP
unnamed: IC89.1 (Q4), IC92.4 (I4)
unnamed: 17.8, Q63.3 (D), TP192.TP
unnamed: 18.10, TP204.TP, X25.15
unnamed: 18.5, D100.2 (-), LED52.K (C), TP199.TP, X25.9
unnamed: D100.1 (+), R369.1
unnamed: IC89.6 (Q5), IC92.3 (I3)
unnamed: 17.4, IC92.10 (O7), TP188.TP
unnamed: IC91.1 (ADJ), R370.1, R377.2, X25.7
unnamed: IC93.6 (-IN), IC93.8 (-IN), R377.1
unnamed: 17.2, Q59.2 (C), TP186.TP
unnamed: 17.1, TP185.TP, X25.1
unnamed: R402.2, X25.16
unnamed: IC89.15 (Q3), IC92.5 (I5)
unnamed: 17.6, IC92.13 (O4), TP190.TP
unnamed: 17.7, IC92.14 (O3), TP191.TP
unnamed: 18.6, JP42.2, TP200.TP
unnamed: LED53.K (C), R390.1
unnamed: LED49.A, LED50.A, LED51.A, LED52.A, LED54.A, R391.1
unnamed: Q57.1 (B), R392.2
unnamed: IC89.3 (Q0), IC92.1 (I1), IC92.2 (I2), Q63.1 (G)
unnamed: IC89.14 (Q1), IC92.6 (I6)
unnamed: 17.3, IC92.11 (O6), TP187.TP
unnamed: Q58.1 (B), Q58.2 (C), Q59.1 (B), R387.1, R388.1, R414.1, X27.2
unnamed: Q59.3 (E), R394.2
unnamed: Q58.3 (E), R393.2
unnamed: IC93.7 (+IN), R378.1, R395.1
unnamed: IC98.2 (-IN), R376.2
unnamed: Q61.1 (B), R396.2
unnamed: Q62.3 (D), R397.2
unnamed: IC91.2 (VO), R370.2
unnamed: IC91.3 (VI), Q60.2 (C)
unnamed: C87.2, D106.2 (-), IC95.2 (TR), IC95.6 (THR), IC99.6 (D2), R400.1
unnamed: IC95.5 (CV), R401.2
unnamed: IC95.3 (Q), IC96.12 (A), R401.1
unnamed: D106.1 (+), R402.1
unnamed: 17.10, D98.2 (-), D99.2 (-), JP45.1, SJ9.1, TP194.TP
unnamed: JP45.2, R403.2, R404.2, SJ9.2
unnamed: IC96.9 (!Q), IC96.11 (B), R407.2
unnamed: C89.1, IC96.14 (T2), R405.1
unnamed: JP41.1, R406.2
unnamed: IC92.15 (O2), R392.1
unnamed: 18.12, R407.1, TP207.TP
unnamed: D103.1 (+), JP43.2
unnamed: D97.2 (-), IC93.2 (OUT), JP42.1, Q62.1 (G), R399.2
unnamed: IC98.1 (OUT), R408.2
unnamed: C90.1, R408.1, R409.1
unnamed: IC98.5 (+IN), R409.2, R410.2
unnamed: IC98.6 (-IN), R411.1, R412.2
unnamed: D104.1 (+), JP44.1
unnamed: JP42.3, R397.1, R398.1
unnamed: R389.1, X25.21
unnamed: Q61.2 (C), R389.2, R413.1
VCC: 6V8.TP, C83.1, IC90.OUT, IC93.3 (V+), IC94.1 (OUT), IC98.8 (V+), R378.2, R381.2, R384.1, R391.2, R411.2; also elsewhere on the board

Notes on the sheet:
6V regulated for Opamps
current source 96mA
ZündungsPlus
Zündugsplus Choke Öldrucklampe Temperaturlampe Ladekontrolllampe Tankgeber (100hm) ABS-Lampe Lampentest Warnlampe Fernlichtlampe Geschwindigkeitssignal Menütaster
DauerPlus Konstant-Strom für LEDs Gang 1 Gang 2 Gang 3 Gang 4 Gang 5 Neutrallampe Blinker rechts Blinker zusammen Blinker links Masse
DauerPlus Batterie 12V (rot weiss) Ganganzeige Signal C (gelb weiss) Ganganzeige Signal B (gelb schwarz) Ganganzeige Signal A (gelb dunkelblau) 12V/350mA zum Starknopf (schwarz grün) Zündungsplus 12V (grün schwarz) Reservelampe (weiss) ABS Leuchte (blau) Ladekontrollleuchte (schaltet auf Masse) (vi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
Masse (braun) Lampentest (schaltet auf Masse)(weiss blau) Fernlichtlampe (12V) (weiss) Drehzahl Zündspule (schwarz blau) Blinker rechts (blau scharz) Masse (braun) Blinker links (blau rot) nicht angeschlossen Tachosiganl zum Blinrelais (balu grün) Tachogeber (gelb) Masse Tachobeger (braun) Tachobel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
4.7V
Stromquelle für Gang LEDs. Für mehr als 12mA muss ein Widerstand "R_user" eingelötet werden. Für weniger muss der 1kOhm SMD Widerstand neben R_user entfernt werden I = 12V/1kOhm(default)+12V/R_user I= 12mA (default) + 12V/R_user Beispiel: R_user Strom in LEDs 1 kOhm 22-26mA ohne 11-13mA
Gang 1
Gang 2
Gang 3
Gang 4
Gang 5
Variante "eine LED leuchtet"
Variante "alle LEDs bis und mit Gang X leuchten"
Klemmleisten Ausgang:
Klemmleisten Ausgang:
an Zündungsplus anhängen (Neutral leuchtet wenn Gang 0 eingelegt und Zündschlüssel steckt )
an Ausgang "Neutrallampe" anhängen
Neutrallampe für eigene Ganganzeige
Externe Beschaltung
Anzeige:
nicht bestückt
rising edge trigger A
BAR
RES
BL resistors
